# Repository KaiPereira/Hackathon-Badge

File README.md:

# Hackathon Badges

These are alchemical, cosmological, PCB hackathon badges I designed in a day for the Fallout hackathon in Shenzhen. Powered by the CH32 MCU, they stack ontop of each other using testpoints and shine through each other to create a sun effect and have cool designs on them!

## Manufacturing

If you're bored and want to manufacture the boards, all of their production files are in their relative folder. I'd suggest getting the boards from JLCPCB with ENIG, and then buying the components from LCSC and hand soldering! 

All the design files are also open-source if you want to make modifications so that they're unique to you, so just go crazy!!

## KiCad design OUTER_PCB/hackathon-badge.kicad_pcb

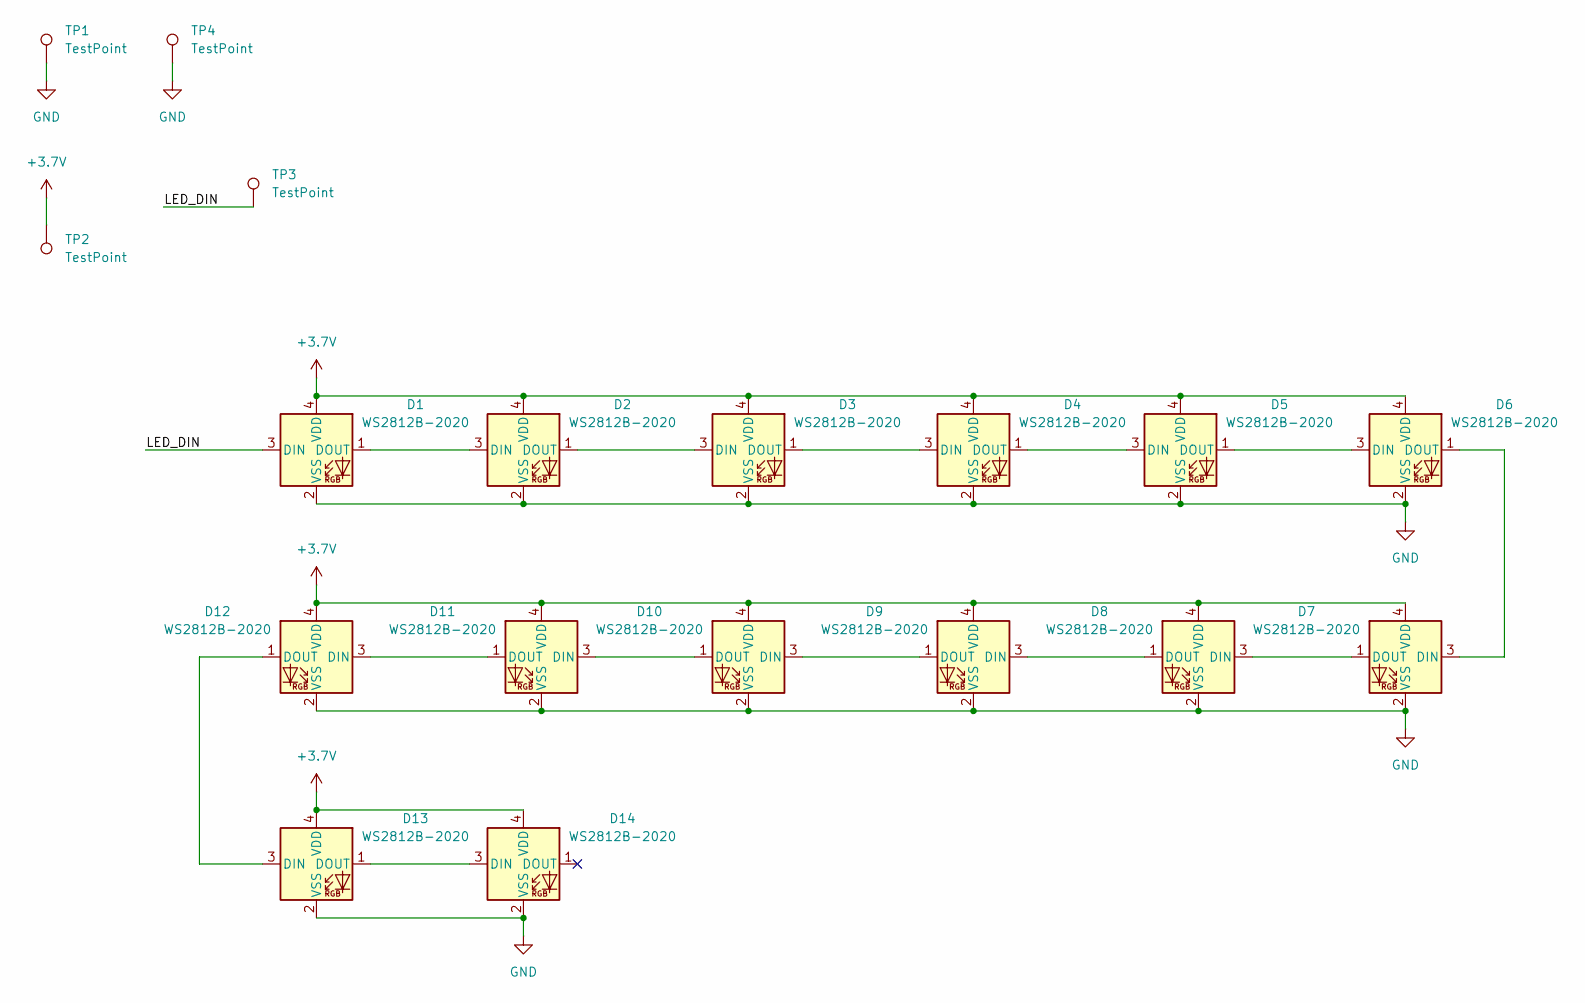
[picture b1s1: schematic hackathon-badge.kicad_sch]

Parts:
D1, D2, D3, D4, D5, D6, D7, D8, D9, D10, D11, D12, D13, D14: WS2812B-2020; LED_WS2812B-2020_PLCC4_2.0x2.0mm
TP1, TP2, TP3, TP4: TestPoint; TestPoint_Pad_4.0x4.0mm

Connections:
+3.7V: D1.4 (VDD), D2.4 (VDD), D3.4 (VDD), D4.4 (VDD), D5.4 (VDD), D6.4 (VDD), D7.4 (VDD), D8.4 (VDD), D9.4 (VDD), D10.4 (VDD), D11.4 (VDD), D12.4 (VDD), D13.4 (VDD), D14.4 (VDD), TP2.1 (1_1)
/LED_DIN: D1.3 (DIN), TP3.1 (1_1)
GND: D1.2 (VSS), D2.2 (VSS), D3.2 (VSS), D4.2 (VSS), D5.2 (VSS), D6.2 (VSS), D7.2 (VSS), D8.2 (VSS), D9.2 (VSS), D10.2 (VSS), D11.2 (VSS), D12.2 (VSS), D13.2 (VSS), D14.2 (VSS), TP1.1 (1_1), TP4.1 (1_1)
unnamed: D1.1 (DOUT), D2.3 (DIN)
unnamed: D2.1 (DOUT), D3.3 (DIN)
unnamed: D3.1 (DOUT), D4.3 (DIN)
unnamed: D4.1 (DOUT), D5.3 (DIN)
unnamed: D5.1 (DOUT), D6.3 (DIN)
unnamed: D6.1 (DOUT), D7.3 (DIN)
unnamed: D7.1 (DOUT), D8.3 (DIN)
unnamed: D8.1 (DOUT), D9.3 (DIN)
unnamed: D9.1 (DOUT), D10.3 (DIN)
unnamed: D10.1 (DOUT), D11.3 (DIN)
unnamed: D11.1 (DOUT), D12.3 (DIN)
unnamed: D12.1 (DOUT), D13.3 (DIN)
unnamed: D13.1 (DOUT), D14.3 (DIN)

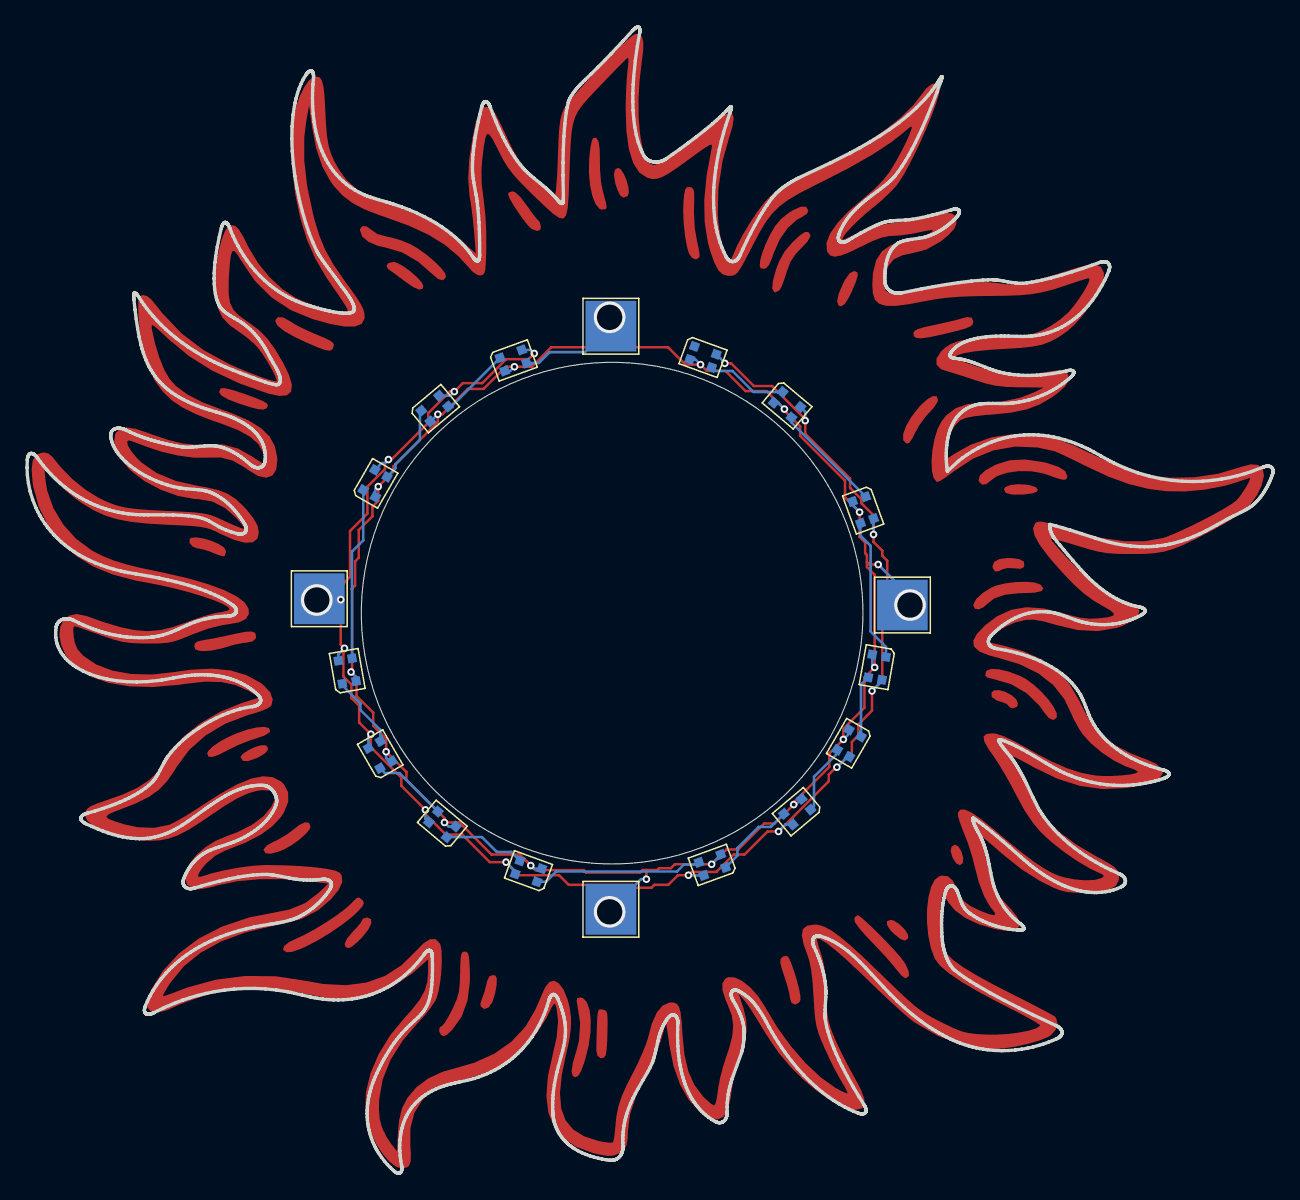
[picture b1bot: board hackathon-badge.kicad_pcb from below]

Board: 2 copper layers, 98.3 x 90.4 mm, 18 parts (18 on the bottom side), 16 nets.

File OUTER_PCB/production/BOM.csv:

"Id";"Designator";"Footprint";"Quantity";"Designation";"Supplier and ref";
1;"D1, D2, D3, D4, D5, D6, D7, D8, D9, D10, D11, D12, D13, D14";"LED_WS2812B-2020_PLCC4_2.0x2.0mm";14;"WS2812B-2020";;;
2;"TP1, TP2, TP3, TP4";"TestPoint_Pad_4.0x4.0mm";4;"TestPoint";;;

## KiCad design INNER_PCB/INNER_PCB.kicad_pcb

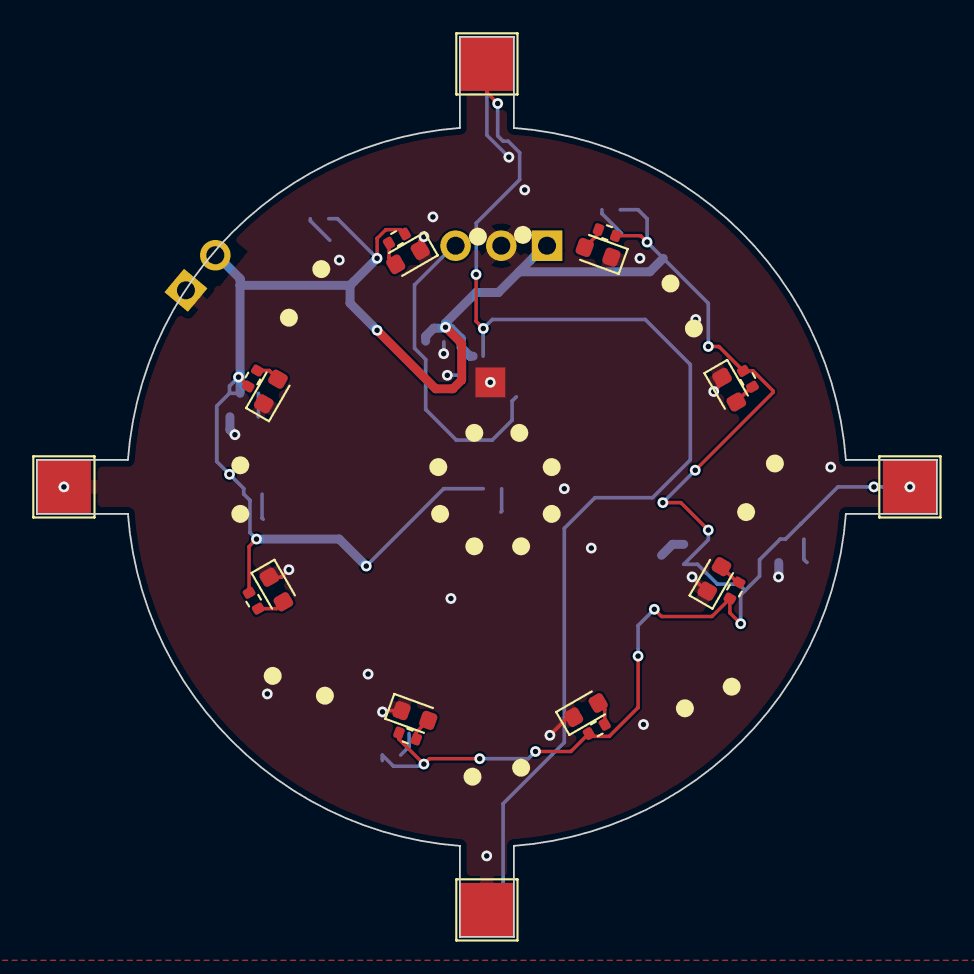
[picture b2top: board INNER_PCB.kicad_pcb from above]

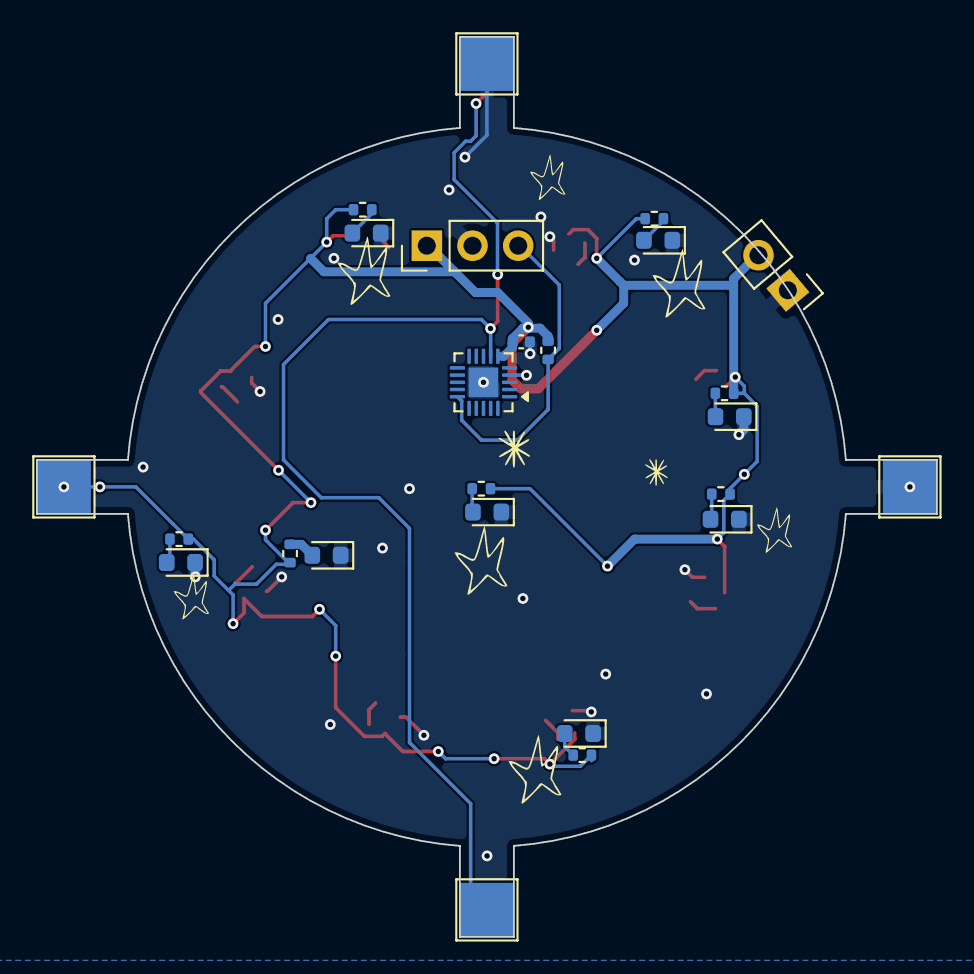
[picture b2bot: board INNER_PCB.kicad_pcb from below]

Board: 2 copper layers, 50.0 x 50.0 mm, 45 parts (25 on the bottom side), 20 nets.

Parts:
C3: 100nF; C_0402_1005Metric
D1, D2, D3, D4, D5, D6, D7, D8, D9, D10, D11, D12, D13, D14, D15, D16: KT-0603Y; LED_0603_1608Metric
J1: Conn_01x03; PinHeader_1x03_P2.54mm_Vertical
J2: Conn_01x02; PinHeader_1x02_P2.54mm_Vertical
R1: 1k; R_0402_1005Metric
R2, R3, R4, R5, R6, R7, R8, R9, R10, R11, R12, R13, R14, R15, R16, R17: 2k; R_0402_1005Metric
TP1, TP2, TP3, TP4, TP5, TP6, TP7, TP8: TestPoint; TestPoint_Pad_3.0x3.0mm
U2: CH32V003FxUx; QFN-20-1EP_3x3mm_P0.4mm_EP1.65x1.65mm_ThermalVias

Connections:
+3.7V: C3.1, J1.1, J2.2, R1.1, R2.1, R3.1, R4.1, R5.1, R6.1, R7.1, R8.1, R9.1, R10.1, R11.1, R12.1, R13.1, R14.1, R15.1, R16.1, R17.1, TP4.1 (1_1), TP8.1 (1_1), U2.6 (VDD)
/LED_DOUT: TP3.1 (1_1), TP6.1 (1_1), U2.7 (PC0)
/SWIO: J1.3, R1.2, U2.15 (SWIO)
GND: C3.2, D1.1 (K), D2.1 (K), D3.1 (K), D4.1 (K), D5.1 (K), D6.1 (K), D7.1 (K), D8.1 (K), D9.1 (K), D10.1 (K), D11.1 (K), D12.1 (K), D13.1 (K), D14.1 (K), D15.1 (K), D16.1 (K), J1.2, J2.1, TP1.1 (1_1), TP2.1 (1_1), TP5.1 (1_1), TP7.1 (1_1), U2.4 (VSS), U2.21 (VSS)
unnamed: D1.2 (A), R2.2
unnamed: D2.2 (A), R3.2
unnamed: D3.2 (A), R4.2
unnamed: D4.2 (A), R5.2
unnamed: D5.2 (A), R6.2
unnamed: D6.2 (A), R7.2
unnamed: D7.2 (A), R8.2
unnamed: D8.2 (A), R9.2
unnamed: D9.2 (A), R10.2
unnamed: D10.2 (A), R11.2
unnamed: D11.2 (A), R12.2
unnamed: D12.2 (A), R13.2
unnamed: D13.2 (A), R14.2
unnamed: D14.2 (A), R15.2
unnamed: D15.2 (A), R16.2
unnamed: D16.2 (A), R17.2

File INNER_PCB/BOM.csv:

"Id";"Designator";"Footprint";"Quantity";"Designation";"Supplier and ref";
1;"C3";"C_0402_1005Metric";1;"100nF";;;
2;"J1";"PinHeader_1x03_P2.54mm_Vertical";1;"Conn_01x03";;;
3;"J2";"PinHeader_1x02_P2.54mm_Vertical";1;"Conn_01x02";;;
4;"R1";"R_0402_1005Metric";1;"1k";;;
5;"TP1, TP2, TP3, TP4, TP5, TP6, TP7, TP8";"TestPoint_Pad_3.0x3.0mm";8;"TestPoint";;;
6;"U2";"QFN-20-1EP_3x3mm_P0.4mm_EP1.65x1.65mm_ThermalVias";1;"CH32V003FxUx";;;
